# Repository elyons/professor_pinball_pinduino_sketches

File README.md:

professor_pinball_pinduino_sketches
===================================

Sketches for the Pinduino sheild for the Arduino.

### TO USE THESE SKETCHES, you will need [pinduino arduino library (github repo)] (https://github.com/elyons/pinduino)

# Welcome

This repo is for various Pinduino sketches.  Pinduino is an Arduino shield to intercept signals from pinball machines and these sketches program the Arduino to interpret those signals for various effects.

# Additional Documents
* [Instructions on Google docs for everything -- programming, building, installing, etc] (https://drive.google.com/drive/folders/0B2njOnd06CCOdlBCVzdiWFZhUVE?resourcekey=0-DgYU0apatzmqqfANwTUaDQ&usp=sharing)
* [Pinduino arduino library] (https://github.com/elyons/pinduino)

# Videos
For a full list of videos, see my YouTube channel for the Pinduino: https://www.youtube.com/playlist?list=PL5ef5BY1kPknPXMwk0Jci0zVyLWubq0l2
* Ironman LED ramps gameplay
* 
* Tron LED ramps gameplay
* 
* Theatre of Magic LED ramps gameplay
*

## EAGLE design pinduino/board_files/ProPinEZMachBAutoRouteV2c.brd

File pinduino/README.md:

Please note that using this library requires Arduino IDE 1.5.8+

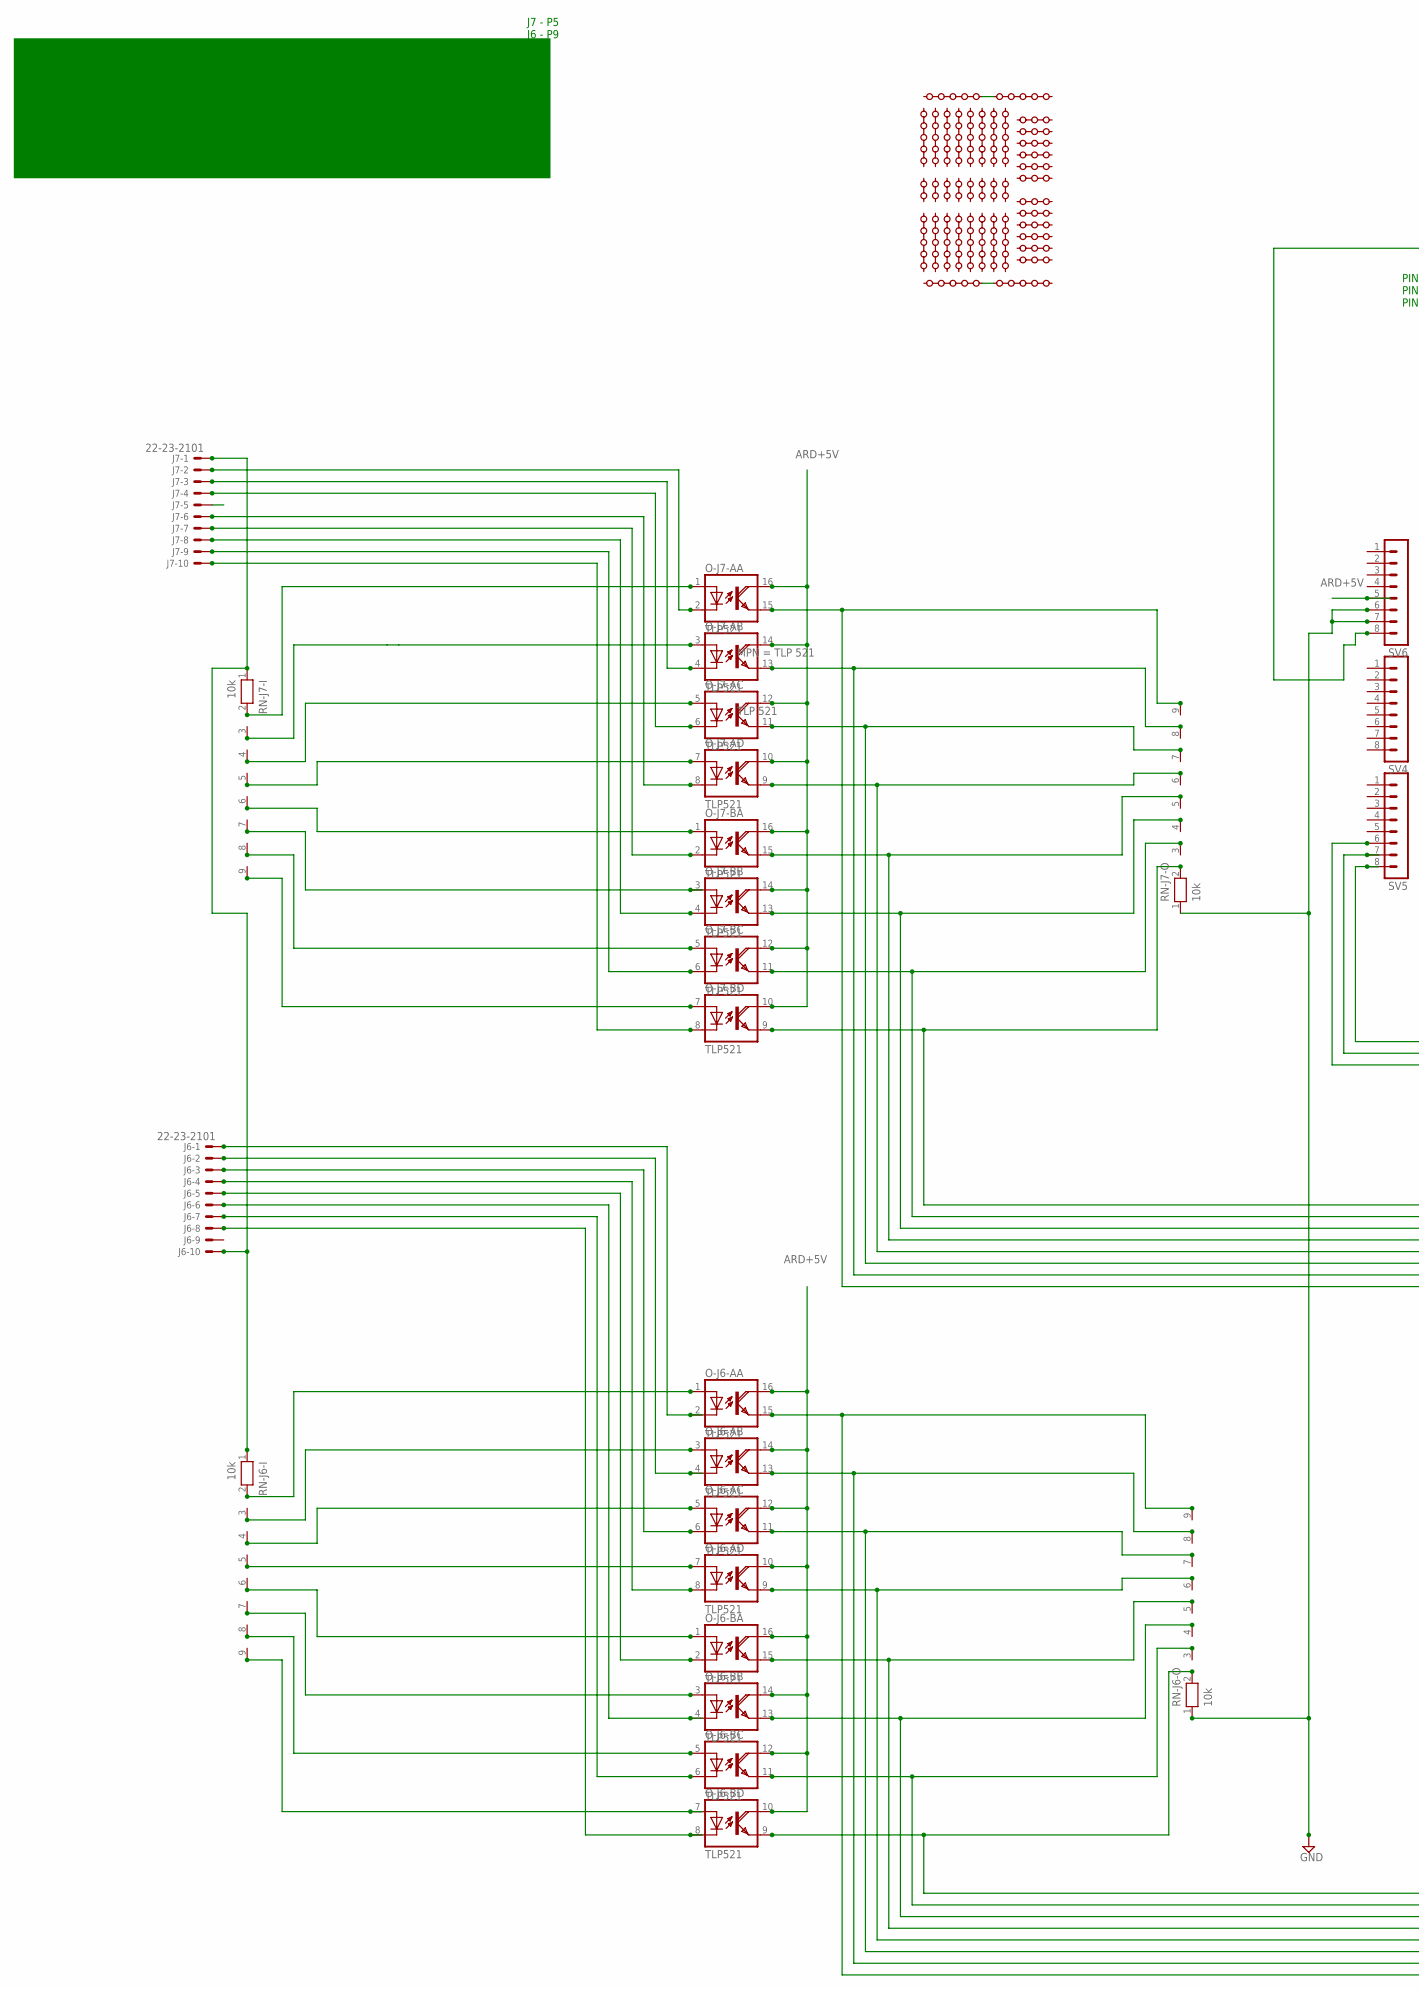
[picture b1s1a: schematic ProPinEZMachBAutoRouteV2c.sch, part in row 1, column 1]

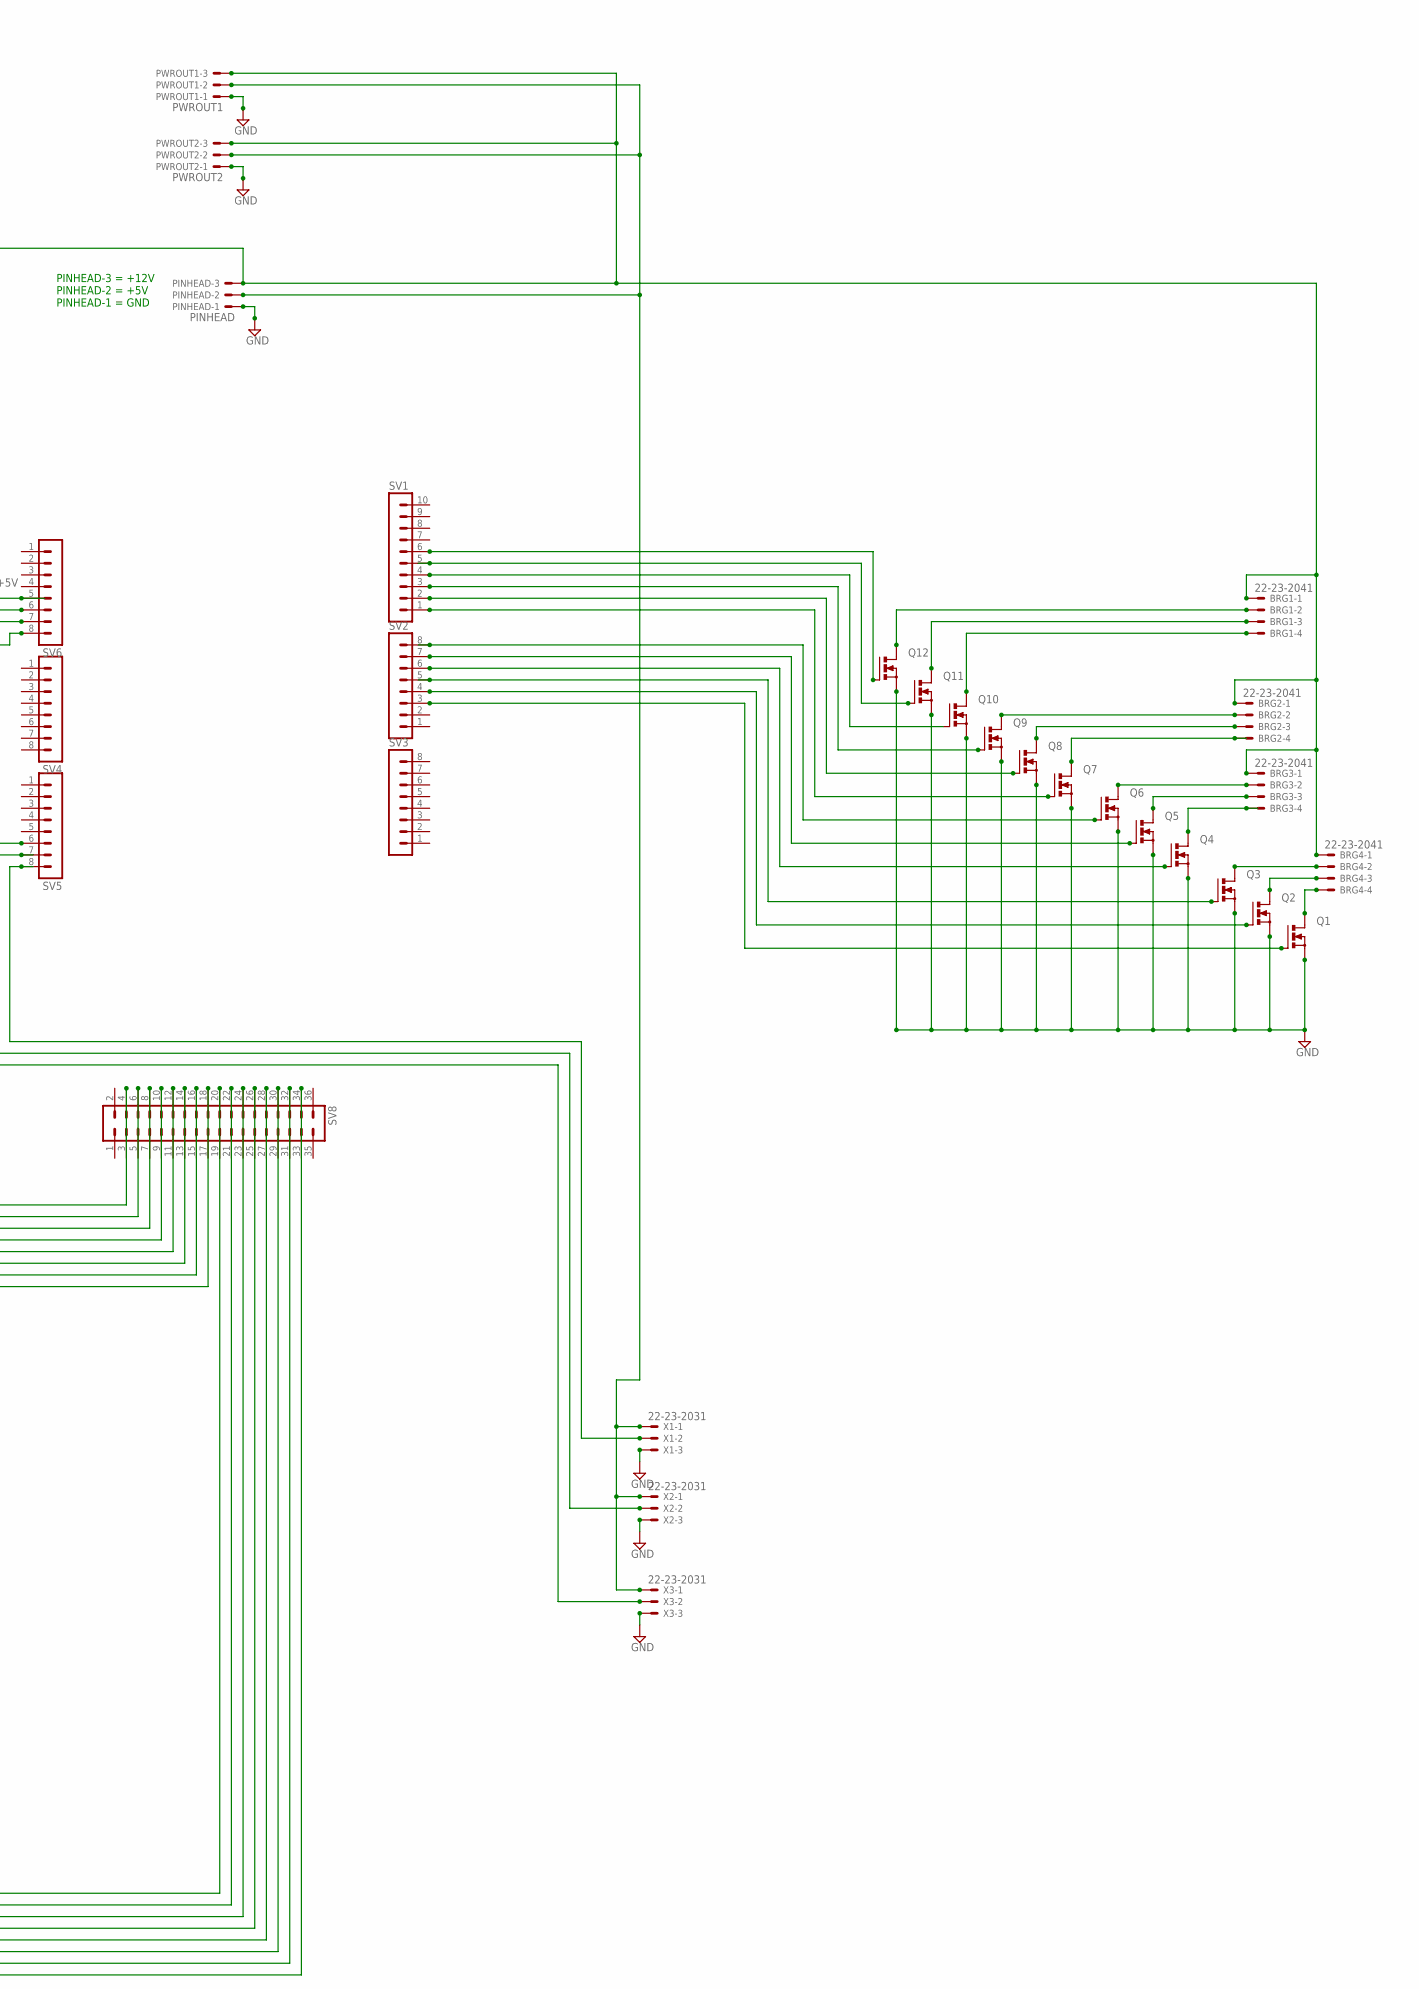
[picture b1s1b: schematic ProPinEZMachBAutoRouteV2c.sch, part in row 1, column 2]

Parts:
BRG1, BRG2, BRG3, BRG4: 22-23-2041
J6, J7: 22-23-2101
O-J6-A, O-J6-B, O-J7-B: TLP521; DIL16
O-J7-A: TLP521; DIL16; MPN TLP 521
P1, P2, P3, P4, P5, P6, P7, P8, P9, P10, P11, P12, P13, P14, P15, P16: PADSTRIP5-HA; PADSTRIP-5H
P17, P18, P19, P20: PADSTRIP5-HB; PADSTRIP-5HC
PINHEAD: PINHEAD; 22-23-2031
PR1, PR2, PR3, PR4, PR5, PR6, PR7, PR8, PR9, PR10, PR23, PR24: PADSTRIP3-H; PADSTRIP-3H
PR13, PR14, PR15, PR16, PR17, PR18, PR19, PR20: PADSTRIP2-H; PADSTRIP-2H
PWROUT1: PWROUT1; 22-23-2031
PWROUT2: PWROUT2; 22-23-2031
Q1, Q2, Q3, Q4, Q5, Q6, Q7, Q8, Q9, Q10, Q11, Q12: PMOSFET_NTO220BV; TO220BV
RN-J6-I, RN-J6-O, RN-J7-I, RN-J7-O: 10k; RN-9
SV1: MA10-1
SV2, SV3, SV4, SV5, SV6: MA08-1
SV8: MA18-2
X1, X2, X3: 22-23-2031

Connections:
ARD+5V: O-J6-A.10 (COL), O-J6-A.12 (COL), O-J6-A.14 (COL), O-J6-A.16 (COL), O-J6-B.10 (COL), O-J6-B.12 (COL), O-J6-B.14 (COL), O-J6-B.16 (COL), O-J7-A.10 (COL), O-J7-A.12 (COL), O-J7-A.14 (COL), O-J7-A.16 (COL), O-J7-B.10 (COL), O-J7-B.12 (COL), O-J7-B.14 (COL), O-J7-B.16 (COL), SV6.5
GND: PINHEAD.1, PWROUT1.1, PWROUT2.1, Q1.S, Q2.S, Q3.S, Q4.S, Q5.S, Q6.S, Q7.S, Q8.S, Q9.S, Q10.S, Q11.S, Q12.S, RN-J6-O.1, RN-J7-O.1, SV6.6, SV6.7, X1.3, X2.3, X3.3
unnamed: P17.5, P18.5
unnamed: O-J7-A.3 (A), RN-J7-I.3
unnamed: O-J7-A.5 (A), RN-J7-I.4
unnamed: O-J7-A.7 (A), RN-J7-I.5
unnamed: O-J7-B.1 (A), RN-J7-I.6
unnamed: O-J7-B.3 (A), RN-J7-I.7
unnamed: O-J7-B.5 (A), RN-J7-I.8
unnamed: O-J7-A.1 (A), RN-J7-I.2
unnamed: J7.2, O-J7-A.2 (C)
unnamed: J7.3, O-J7-A.4 (C)
unnamed: J7.4, O-J7-A.6 (C)
unnamed: J7.6, O-J7-A.8 (C)
unnamed: J7.7, O-J7-B.2 (C)
unnamed: J7.8, O-J7-B.4 (C)
unnamed: J7.9, O-J7-B.6 (C)
unnamed: J7.10, O-J7-B.8 (C)
unnamed: J6.10, J7.1, RN-J6-I.1, RN-J7-I.1
unnamed: J6.1, O-J6-A.2 (C)
unnamed: J6.2, O-J6-A.4 (C)
unnamed: J6.3, O-J6-A.6 (C)
unnamed: J6.4, O-J6-A.8 (C)
unnamed: J6.5, O-J6-B.2 (C)
unnamed: O-J7-B.7 (A), RN-J7-I.9
unnamed: J6.6, O-J6-B.4 (C)
unnamed: J6.7, O-J6-B.6 (C)
unnamed: J6.8, O-J6-B.8 (C)
unnamed: O-J6-A.1 (A), RN-J6-I.2
unnamed: O-J6-A.3 (A), RN-J6-I.3
unnamed: O-J6-A.5 (A), RN-J6-I.4
unnamed: O-J6-A.7 (A), RN-J6-I.5
unnamed: O-J6-B.1 (A), RN-J6-I.6
unnamed: O-J6-B.3 (A), RN-J6-I.7
unnamed: O-J6-B.5 (A), RN-J6-I.8
unnamed: O-J6-B.7 (A), RN-J6-I.9
unnamed: O-J7-A.9 (EMI), RN-J7-O.6, SV8.12
unnamed: O-J7-A.11 (EMI), RN-J7-O.7, SV8.14
unnamed: O-J7-A.13 (EMI), RN-J7-O.8, SV8.16
unnamed: O-J7-A.15 (EMI), RN-J7-O.9, SV8.18
unnamed: O-J7-B.9 (EMI), RN-J7-O.2, SV8.4
unnamed: O-J7-B.11 (EMI), RN-J7-O.3, SV8.6
unnamed: O-J7-B.13 (EMI), RN-J7-O.4, SV8.8
unnamed: O-J7-B.15 (EMI), RN-J7-O.5, SV8.10
unnamed: P19.5, P20.5
unnamed: Q10.G, SV1.4
unnamed: SV5.8, X1.2
unnamed: PINHEAD.2, PWROUT1.2, PWROUT2.2, X1.1, X2.1, X3.1
unnamed: SV5.7, X2.2
unnamed: SV5.6, X3.2
unnamed: BRG4.2, Q3.D
unnamed: BRG3.4, Q4.D
unnamed: BRG1.2, Q12.D
unnamed: Q1.G, SV2.3
unnamed: BRG3.3, Q5.D
unnamed: BRG3.2, Q6.D
unnamed: O-J6-A.15 (EMI), RN-J6-O.9, SV8.34
unnamed: O-J6-A.13 (EMI), RN-J6-O.8, SV8.32
unnamed: O-J6-A.11 (EMI), RN-J6-O.7, SV8.30
unnamed: O-J6-A.9 (EMI), RN-J6-O.6, SV8.28
unnamed: O-J6-B.15 (EMI), RN-J6-O.5, SV8.26
unnamed: O-J6-B.13 (EMI), RN-J6-O.4, SV8.24
unnamed: O-J6-B.11 (EMI), RN-J6-O.3, SV8.22
unnamed: O-J6-B.9 (EMI), RN-J6-O.2, SV8.20
unnamed: Q2.G, SV2.4
unnamed: Q3.G, SV2.5
unnamed: Q4.G, SV2.6
unnamed: Q5.G, SV2.7
unnamed: BRG2.4, Q7.D
unnamed: BRG2.3, Q8.D
unnamed: BRG2.2, Q9.D
unnamed: BRG1.1, BRG2.1, BRG3.1, BRG4.1, PINHEAD.3, PWROUT1.3, PWROUT2.3, SV6.8
unnamed: Q6.G, SV2.8
unnamed: Q7.G, SV1.1
unnamed: Q8.G, SV1.2
unnamed: BRG4.4, Q1.D
unnamed: Q9.G, SV1.3
unnamed: BRG4.3, Q2.D
unnamed: Q11.G, SV1.5
unnamed: BRG1.4, Q10.D
unnamed: BRG1.3, Q11.D
unnamed: Q12.G, SV1.6

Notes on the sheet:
TEST
J7 - P5
J7 - P5 J6 - P9
PINHEAD-3 = +12V PINHEAD-2 = +5V PINHEAD-1 = GND

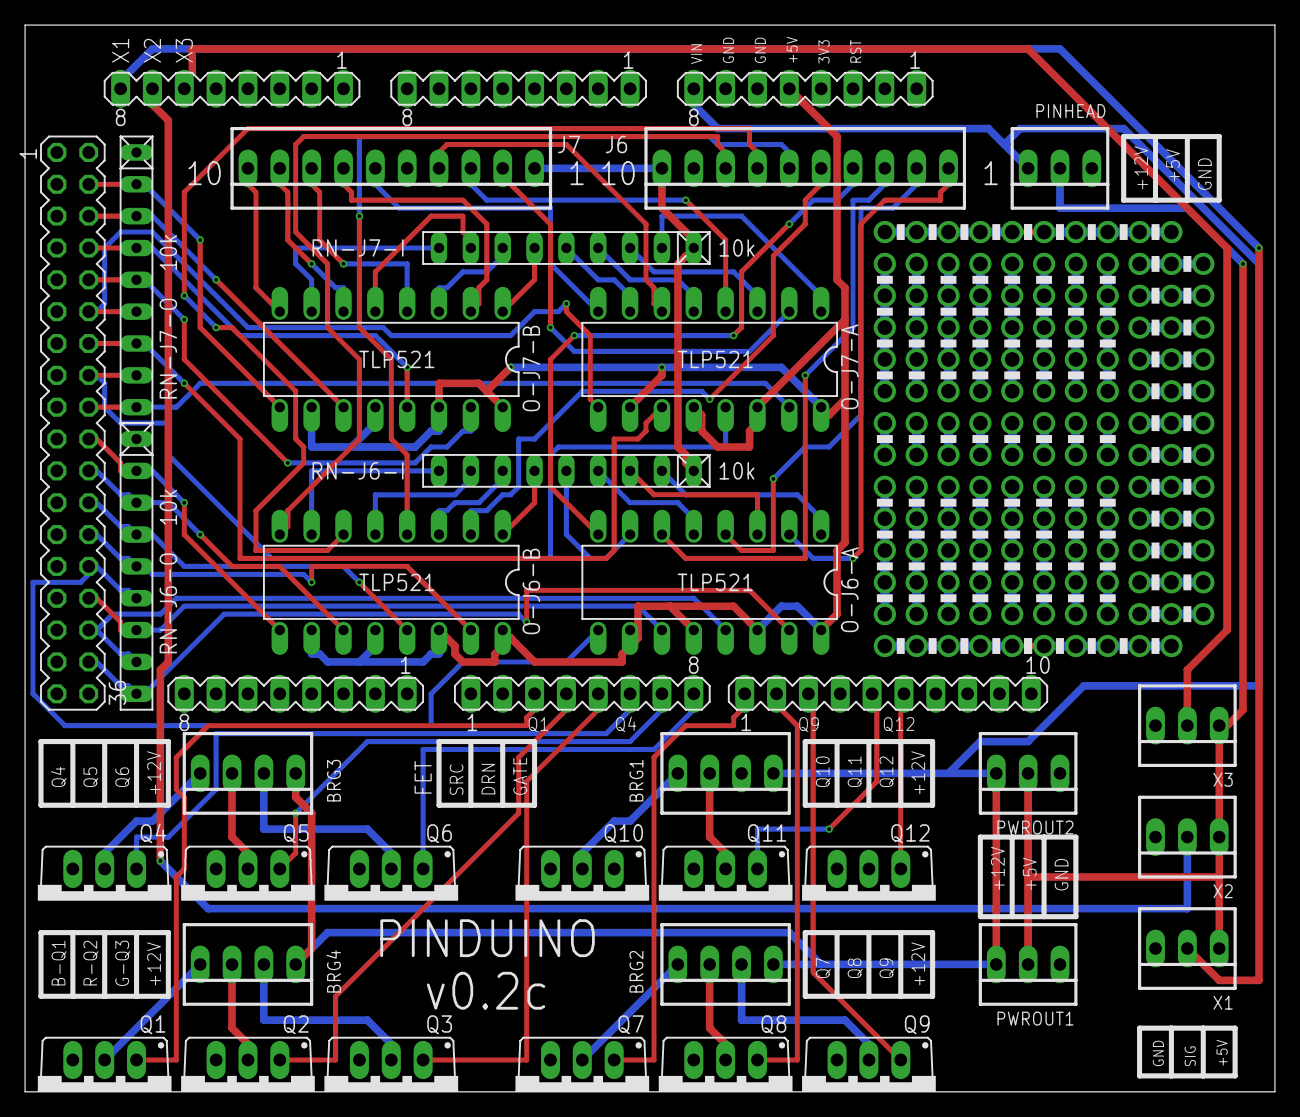
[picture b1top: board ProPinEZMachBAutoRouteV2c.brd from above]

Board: 2 copper layers, 99.7 x 85.1 mm, 79 parts (0 on the bottom side), 82 nets.

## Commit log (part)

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2015-02-05 updated to include object for monitoring pinball states
2015-02-05 updated to support pinduinoPins object
2015-02-05 updated to support pinduinoPins object, including running checks on pinState inside of long loops
2015-02-07 changed function names and added new functions: get, numPins, J6, J7
2015-02-07 fixed semicolon and main .ino weirdness
2015-02-07 cleaned up code
2015-02-07 added functions resetPin and any
2015-02-08 Changes for Continuous functions
2015-02-08 added linked list options for previous and next Addresable LED strips. Functions next, previous, setNext, setPrevious
2015-02-08 Finished up the Continuous Speaker Mods
2015-02-14 added functions resetJ6 and reset J7
2015-02-15 added functions fadeRGB2RGB; fadeColor2Color (not tested yet -- need another mega)
2015-02-16 Added Bullet FX
2015-02-17 formatting changes and added sub chase2ColorCont
2015-02-17 add sub chase2ColorCont
2015-02-17 moved old code to its own directory
2015-02-22 renamed XMen library
2015-02-22 fixed folder name for ToM
2015-02-22 Ironman interactive ramps, uses board v0.2 and pinduino library
2015-02-26 decreased fade time to 50 ms
2015-02-26 formatting change
2015-03-03 used to test if Pinduino is working correction by changing an LED strip red when an optoisolator is triggered
2015-03-03 interactive lights for backbox strip
2015-03-15 Added a constructor with no parameters
    Added a new constructor for the pinduino class that requires no
    parameters, to make it more obvious that you don't need to set up
    addressable strips if you don't have them.
2015-03-15 Added the prototype for the constructor with no parameters
2015-03-15 Retrofitted the RGBStrip class
    Fixed up the RGBStrip class to start using true RGB values (0-255).
    These changes are backwards compatible with all older code written
    against the class.
2015-03-20 in sub update, skipping checking J7-10 due to noise from LOTR
2015-03-20 added checks for pin state activity in background sequence
2015-03-20 initial import
2015-03-25 v2. Updated many of the lighten affects to better suit the game play
2015-04-17 commented out debugging messages
2015-06-10 added functions fadeOutAllAdr and fadeInAllAdr
2015-06-10 Added functions fadeInAllAdr and fadeOutAllAdr
2015-06-10 lots of changes -- much better use of lighting effects
2015-06-11 updated to have lighting effect be synced with ramp lighting effects
2015-09-13 updated flashing of ramps when pops flasher is triggered. Only flashes once per trigger and light is dimmer.
2015-09-24 gerber files for SEEED studio
2015-10-06 added sub fadeAllAdrRGB2RGB
2015-10-06 added sub fadeAllAdrColor2Color
2015-10-06 updated new effects in quora and recognizer
2015-10-07 updated some routines for better checking of LED position; added sub AddressableStrip::chase2RGBFromPoint
2015-10-07 fixed some bugs, added chaseAllAdr2RGBFromPoint
2015-10-07 added new functions for LED effects across all addressable LED strips
2015-10-09 minor updates to some effects
2015-10-16 added routine for video game
2015-10-17 added background sequence for attract mode
2016-01-18 Added flasher effects
2016-02-15 adding an iframe test
2016-02-15 removed iframe test
2016-03-15 fixed markdown error
2016-04-03 added support for Arduino Nano based boards
2016-04-03 added support for Nano based Pinduinos
2016-04-03 updated LED length for wrapping LEDs around ramps instead of running on bottom; updated to use Nano based pinduino
2016-04-03 added functions to get/reset values from J126 for WPC games
2016-04-03 updated tp use Nano based pinduino
2016-05-13 fixed typo
2016-05-13 new version based on pinduino v0.3. Includes expanded functions
2016-05-23 updated for pinduino v0.3
2016-06-21 added note that pinduino v0.3 is supported
2016-10-23 updated comment
2016-10-23 updated to nano board v0.3
2016-10-23 updated to pinduino v0.3, updated lights to turn white when there is no activity -- brightens playfield
2016-10-23 default on for printing pinstates
2016-11-19 shorted times on background lighting effects on face; updated blue chase up ramp to be purple->blue fade
2016-11-19 added support for second LED strip to be placed under backbox near backpanel; modified some colors on the gumball machine
2016-12-06 moved board files to top level directory
2016-12-06 updated with paragraph, URL, and category
2016-12-06 moved to new repo: https://github.com/elyons/pinduino. This will make it easier to have it added to arduino's library list for easier importing by others
2016-12-06 added more links to pinduino library
2016-12-06 Remove foo.txt
2016-12-15 changed the aLEDNum2 count to 0 as this strip is not used in the code
2016-12-24 updated number of leds used in the build
2016-12-24 correcting some formating
2016-12-27 added link to YouTube channel
2017-03-14 updated so chance sequence is on at when pinduino starts up
2017-03-16 changed some effects from white to blue, and dimmed the usage of white from max down to 2/3 power. This lowers overall current draw from the setup and lowers the chance of MPU reset.
2017-05-31 massive update to lighting effects
2017-07-14 updated for arduino nano
2017-10-09 updated version of shield in comments
2017-10-09 turned on attract mode by default, removed functions for magnets as they are not used
2017-10-09 updated so attract sequence is on at start without wait
2017-10-09 initial import: beta code
2017-10-15 added support for ramp LEDS on LED channel 2
2017-10-25 Edits by Paul. Added comments for flashers being triggered; changed snake flasher J6-6 from red to green
2017-10-29 updated with new effects.
2017-10-30 added code to handle Magneto light coming on after gameplay so the game returns to the attract mode
2017-10-30 removed code when orbit diverter activates; changed colors during attract mode, added better handling of returning to attract mode after game ends
2017-11-10 added a trigger flag for J6-3
2017-11-10 changed wait time for attact sequence from 30 to 60 seconds
2017-11-14 minor change, removing an unused parameter
2017-11-22 massive update
2017-11-23 added option for additional LEDs along the iceman ramp; updated attract sequence colors from white to yellow
2017-12-17 minor update -- shorted the length of some effects
2017-12-17 several small changes in lighting colors, added dataStream lighting effects to attact sequence
2017-12-29 updated date and some comments
2017-12-29 updated to reflect new lighting effects and support for both ramps
2018-01-06 added sparkle effect for attact to LED port 2
2018-02-02 updated to pinduino v0.3 and various lighting effects
2018-02-02 updated attact lighting sequence to sparkle
2018-02-05 initial iport
2018-05-09 initial import (code by Mike Mitchell)
2018-05-12 turned attract sequence on at start, removed a 25 cycle check on pinstate updates to a single cycle per loop
2018-05-22 big update on colors and effects
2018-06-07 added code to clear LEDs before running a triggering effect to remove sparkels from the ramp after gameplay begins. Updated attract mode sequence to only hold orange color for half the sparkleTime. U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
2018-06-07 added a reset to timeLastEvent in attract mode so the background function will reset after completing full cycle
2018-06-08 removed debugging printouts
2018-06-08 Added a fade in to skill shot event
2018-06-22 updated template to be cleaner
2018-06-22 initial import for White Water
2018-07-14 updated dataStream call in backgroundChase to work well with updates to that function in the core pinduino library
2018-07-15 updated to have a sparkle attact mode
2018-10-14 updated speed of water fall effect, added another effect for whirlpool
2018-11-22 minor update on random even tot have the chase event triggered that runs down the main ramp
2018-11-22 commented out debugging statement
2018-11-23 Updated various lighting effects
2018-11-24 added new effect for when both cannon motors are running, removed white from attract mode (just cycles blue and purple), changed borg effect when both left and right borg flashers are active (not jus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
2018-12-28 uppdated attractMode lighting effets
2018-12-28 cleaned up code, no functional changes
2019-01-06 Added 2 sec delay to keep lights red when cannons are moving
2019-01-06 removed debugging output
2019-01-26 updated sensing of dome flasher to be ignored in attract mode
2019-01-26 updated to turn off the shaker when after the dome flasher is triggered; turned off shaker from flippers
2019-01-27 updated authors, cut back on the time for some of the shaking effects
2019-01-27 added pulse delays after shaker is activated
2019-03-15 dialed back the white brightness when the strips are all on during gameplay
2019-04-20 updated with comment at top
2019-04-24 updated recognizer colors to be just orange and not fade orange to red
2019-04-26 added a fade in/out to blue for both LEDs for the zen flasher
2019-05-16 updated background effects
2019-05-16 added effects to control a sparkle on LED2
2019-07-22 updated color effects for Rudy Lamp light
2019-09-22 updated bugs where LED1 was used instead of LED2; updated timing of some effects for LED2
2019-09-22 updated comments to reflect code rather than source file used to build this sketch
2019-09-22 updated date and added credit to MarklarD for the suggestion.
2019-10-24 updated background mode with sparkle effect
2020-01-25 Some minor formatting changes
2020-02-22 updated to test both LED1 and LED2
2020-02-23 added ->clear to LED1 for clearing the color of the fishtank states.
2020-04-26 made both ramps the same length of LEDs in case someone installs more LEDs on the right ramp
2020-04-26 initial import: substituted blue color for ice blue (lighter blue)
2020-04-26 decreased the density of sparkles for the cabinet LEDs when the background effect is running
2020-05-17 updated attract mode for stadium lights
2020-09-16 Update CFTBL-Ramp-Lazzari.ino
    Added new author name
2020-09-26 updated attract mode to only be blue
2020-09-26 removed some whitespace
2020-09-26 updated code formating
2021-02-24 Added a simple colour effect
    Added a simple colour effect for testing in metamorphasisEffect() at the end
2021-02-24 Update BoP_heartbeat_update.ino
    Removed duplicated line.
2021-11-20 removed J6-8 event
2021-11-20 added in code to make sure LED strip resets to white after trigger
2022-03-26 update LED1 length
2022-03-26 Updated attract mode colors and functions
2022-05-08 updated test to use sparkle effect for faster response times
2022-05-31 Added code to switch between sparkle and data stream effects for attract mode
2022-10-30 updated color effects when visor motor is running
2022-10-30 updated testing effect
2022-10-30 added in code to make it easier for people to switch attract mode from dataStream to sparkle effect
2022-12-11 Initial import. Modified original Pinbot code to have a 60LED strip on LED-2
2023-02-26 various updates
2023-02-26 updated side rail LED length
2023-02-26 updated attrack mode effects
2023-03-17 Lots of stuff
2023-03-18 updated directory and file names to remove spaces and dashes for Arduino IDE on linux to work with sketches
2023-05-22 Update TheatreofMagicinteractiverampsv2.ino
    Added comments for what flashers trigger various pins on the Pinduino
2025-02-16 updated with change date and credits
2025-02-16 updated to turn ramp to purple after an effect is run during gameplay
2025-02-16 minor formatting changes
2025-02-16 fixed minor bug in sparkle effect call
2025-02-16 stubbed out all code for detecting pinstate events. Added in information on each circuit for Taxi for P11 (A/C) and P12
2025-02-16 added in some stub effects for various game activity
2025-02-16 moved logic for turning ramp purple and face white during gameplay. Now part of the initial check (if/else) for if attract mode is on.
2025-02-16 removed turning ramp purple during gameplay. Having problems keeping that solid without intermittent flashing
2025-02-17 added call so ramps turn purple when not running an effect during gameplay
2025-02-17 added second LED strip for attract mode
2025-11-16 removed trigger flag from conditionals that aren't used for lighting effects
2025-11-16 fixed comment typo
2025-11-17 further updated to lighting effects
2025-11-20 updated lighting effects for PotD
2025-12-17 updated function 'background' to 'attract_mode'; updated attract mode to use a sparkle white for the face LEDs
